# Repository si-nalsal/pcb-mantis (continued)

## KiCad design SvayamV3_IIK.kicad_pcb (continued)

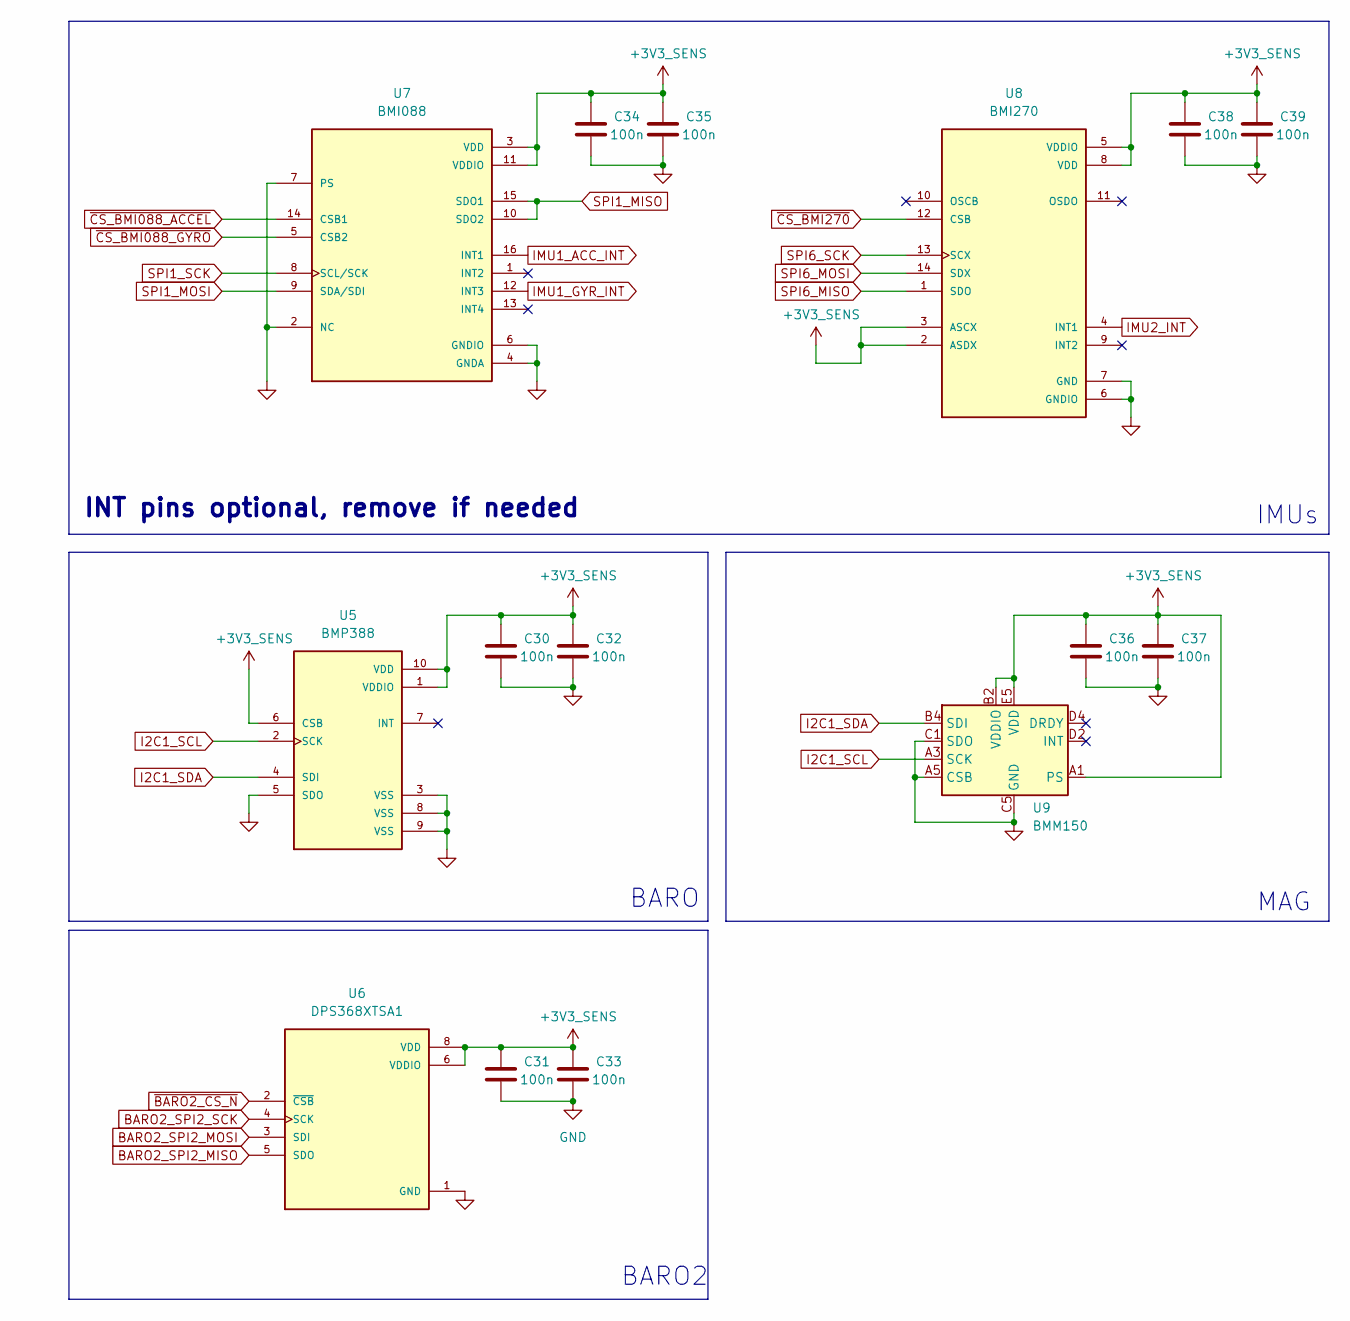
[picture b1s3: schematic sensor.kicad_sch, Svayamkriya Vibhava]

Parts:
C30, C31, C32, C33, C34, C35, C36, C37, C38, C39: 100n; C_0402_1005Metric; MPN CL05B104KB54PNC; LCSC C307331
U5: BMP388; XDCR_BMP388; PARTREV 1.1; LCSC C779278
U6: DPS368XTSA1; XDCR_DPS310XTSA1; MPN DPS368XTSA1; LCSC C3232508
U7: BMI088; PQFN50P450X300X100-16N; MPN BMI088; LCSC C194919
U8: BMI270; XDCR_BMI270; MPN BMI270; LCSC C2836813
U9: BMM150; WLCSP-12_1.56x1.56mm_P0.4mm; MPN BMM150; LCSC C171681

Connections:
+3V3_SENS: C30.1, C31.1, C32.1, C33.1, C34.1, C35.1, C36.1, C37.1, C38.1, C39.1, U5.1 (VDDIO), U5.6 (CSB), U5.10 (VDD), U6.6 (VDDIO), U6.8 (VDD), U7.3 (VDD), U7.11 (VDDIO), U8.2 (ASDX), U8.3 (ASCX), U8.5 (VDDIO), U8.8 (VDD), U9.A1 (PS), U9.B2 (VDDIO), U9.E5 (VDD); also elsewhere on the board
BARO2_SPI2_MISO: U6.5 (SDO); also elsewhere on the board
BARO2_SPI2_MOSI: U6.3 (SDI); also elsewhere on the board
BARO2_SPI2_SCK: U6.4 (SCK); also elsewhere on the board
GND: C30.2, C31.2, C32.2, C33.2, C34.2, C35.2, C36.2, C37.2, C38.2, C39.2, U5.3 (VSS), U5.5 (SDO), U5.8 (VSS), U5.9 (VSS), U6.1 (GND), U6.7 (GND), U7.2 (NC), U7.4 (GNDA), U7.6 (GNDIO), U7.7 (PS), U8.6 (GNDIO), U8.7 (GND), U9.A5 (CSB), U9.C1 (SDO), U9.C5 (GND), U9.E1 (GND), U9.E3 (GND); also elsewhere on the board
I2C1_SCL: U5.2 (SCK), U9.A3 (SCK); also elsewhere on the board
I2C1_SDA: U5.4 (SDI), U9.B4 (SDI); also elsewhere on the board
IMU1_ACC_INT: U7.16 (INT1); also elsewhere on the board
IMU1_GYR_INT: U7.12 (INT3); also elsewhere on the board
IMU2_INT: U8.4 (INT1); also elsewhere on the board
SPI1_MISO: U7.10 (SDO2), U7.15 (SDO1); also elsewhere on the board
SPI1_MOSI: U7.9 (SDA/SDI); also elsewhere on the board
SPI1_SCK: U7.8 (SCL/SCK); also elsewhere on the board
SPI6_MISO: U8.1 (SDO); also elsewhere on the board
SPI6_MOSI: U8.14 (SDX); also elsewhere on the board
SPI6_SCK: U8.13 (SCX); also elsewhere on the board
~BARO2_CS_N: U6.2 (~CSB); also elsewhere on the board
~CS_BMI088_ACCEL: U7.14 (CSB1); also elsewhere on the board
~CS_BMI088_GYRO: U7.5 (CSB2); also elsewhere on the board
~CS_BMI270: U8.12 (CSB); also elsewhere on the board

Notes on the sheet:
MAG
BARO2
IMUs
BARO
INT pins optional, remove if needed

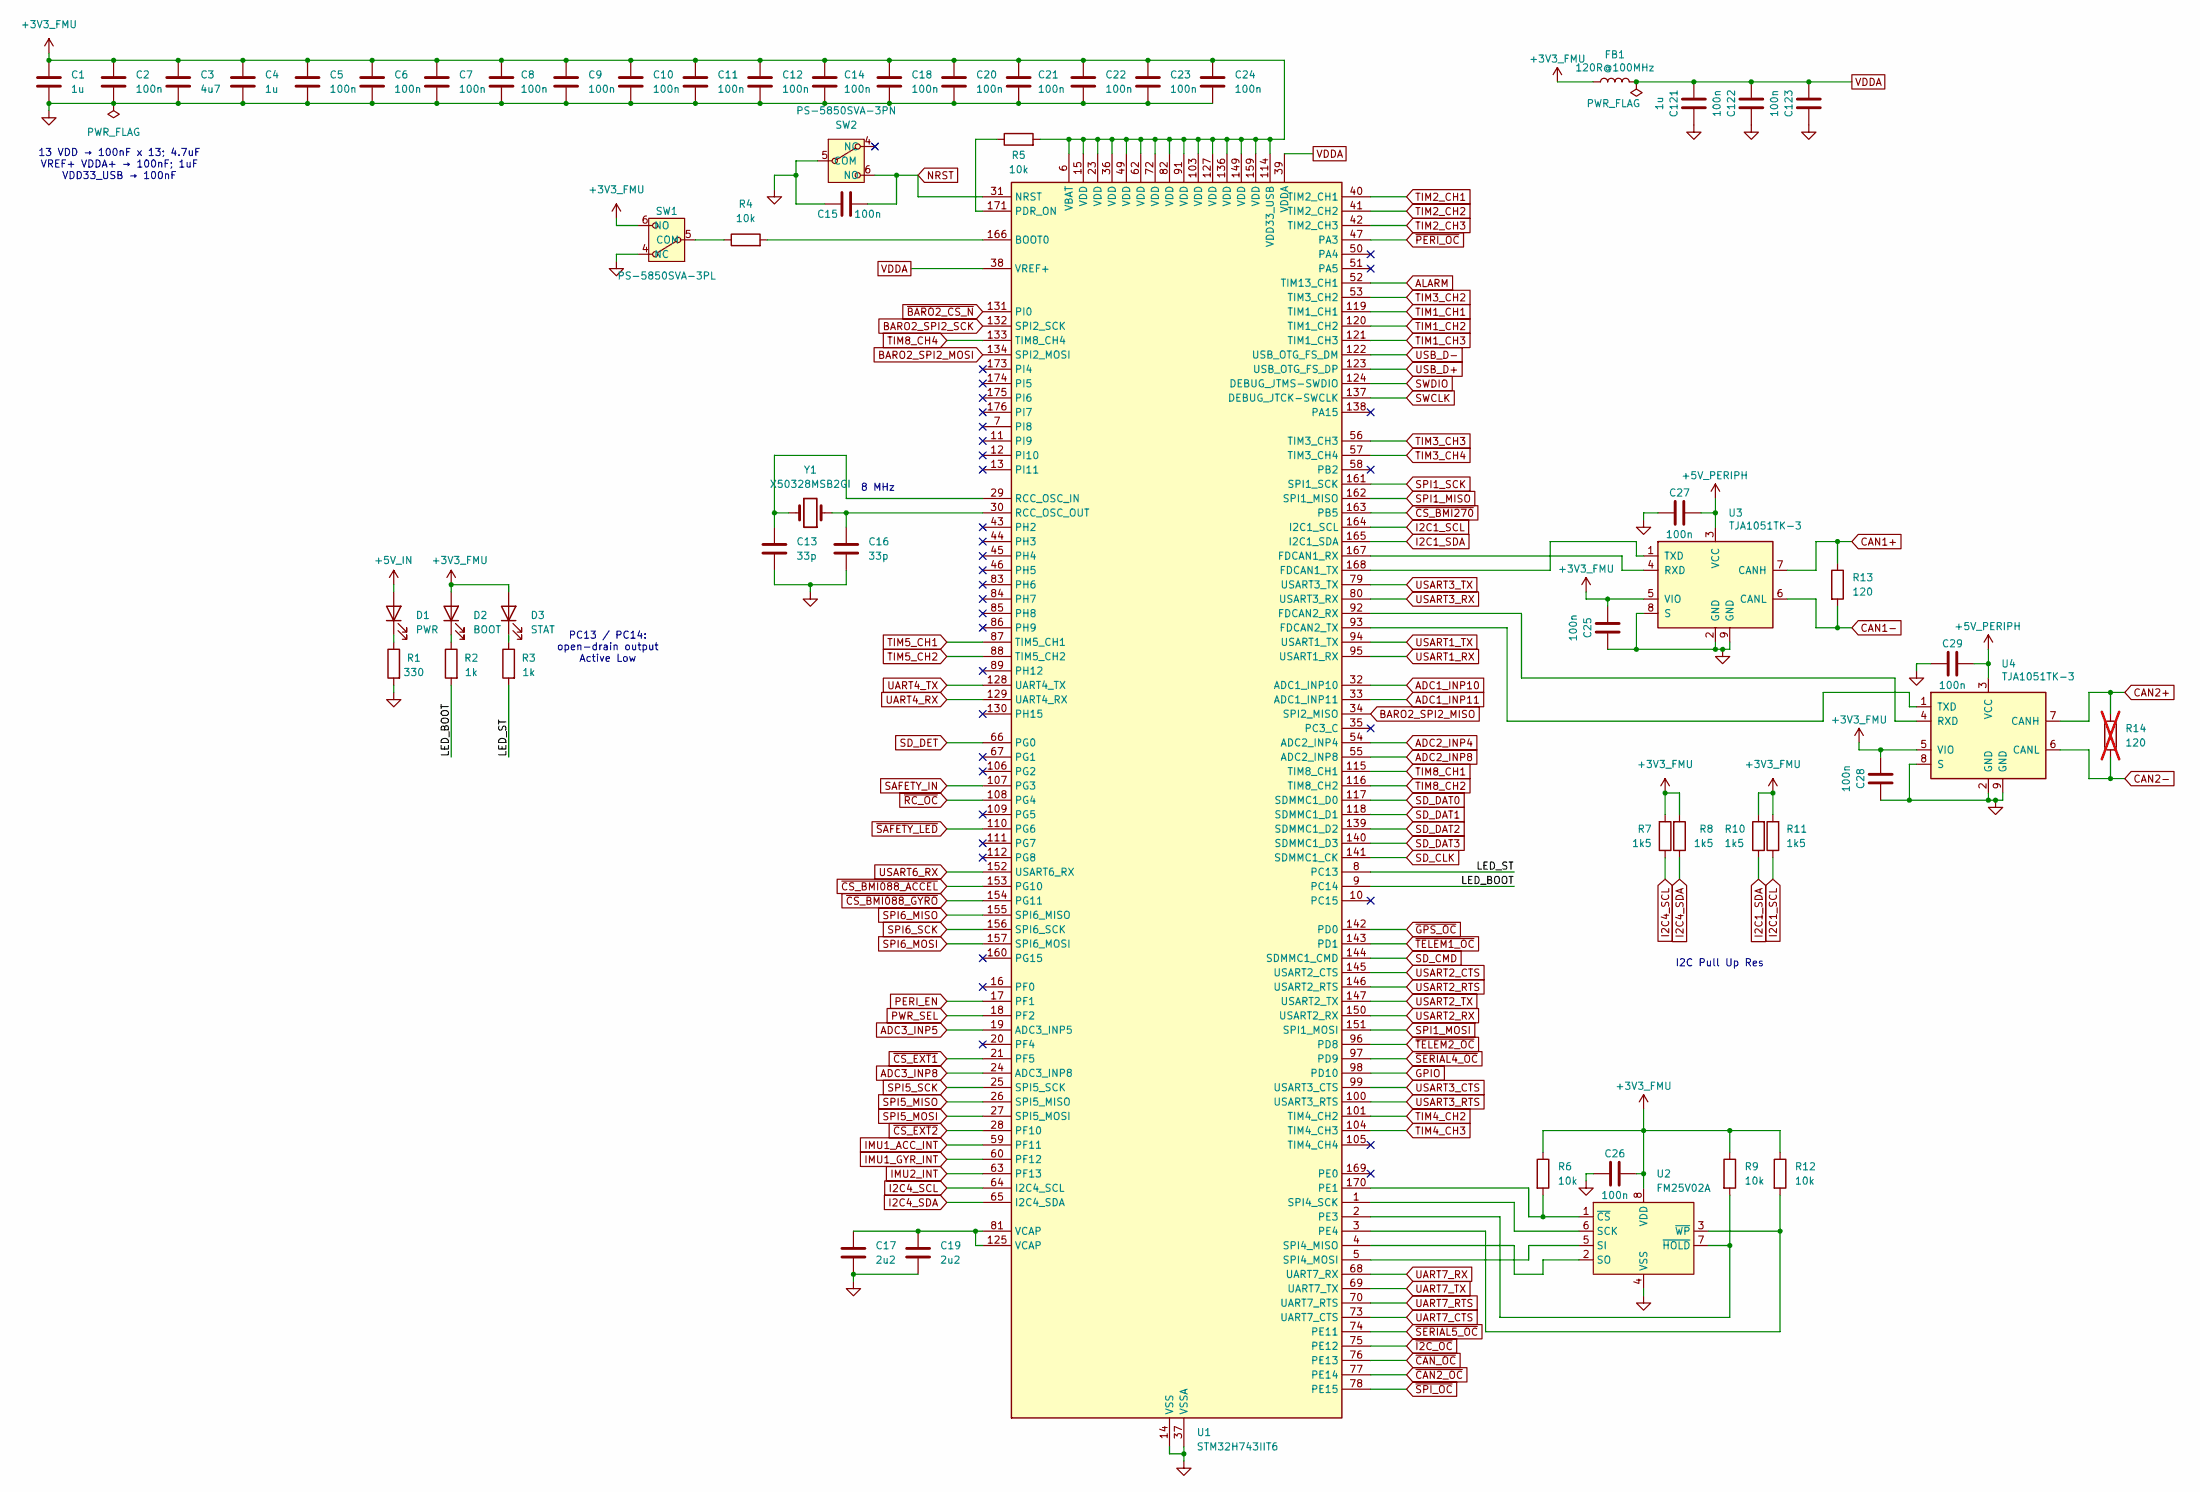
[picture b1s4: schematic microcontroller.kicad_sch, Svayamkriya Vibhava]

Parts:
C1, C4, C121: 1u; C_0603_1608Metric; MPN CL10A105KB8NNNC; LCSC C15849
C2, C5, C6, C7, C8, C9, C10, C11, C12, C14, C15, C18, C20, C21, C22, C23, C24, C25, C26, C27, C28, C29, C122, C123: 100n; C_0402_1005Metric; MPN CL05B104KB54PNC; LCSC C307331
C3: 4u7; C_0603_1608Metric; MPN CL10A475KO8NNNC; LCSC C19666
C13, C16: 33p; C_0402_1005Metric; MPN 0402CG330J500NT; LCSC C1562
C17, C19: 2u2; C_0603_1608Metric; MPN CL10A225KO8NNNC; LCSC C23630
D1: PWR; D_0603_1608Metric; MPN NCD0603R1; LCSC C84263
D2: BOOT; D_0603_1608Metric; MPN NCD0603R1; LCSC C84263
D3: STAT; D_0603_1608Metric; MPN NCD0603R1; LCSC C84263
FB1: 120R@100MHz; L_0402_1005Metric; MPN BLM15PD121SN1D; LCSC C76891
R1: 330; R_0402_1005Metric; MPN 0402WGF3300TCE; LCSC C25104
R2, R3: 1k; R_0402_1005Metric; MPN 0402WGF1001TCE; LCSC C11702
R4, R5, R6, R9, R12: 10k; R_0402_1005Metric; MPN 0402WGF1002TCE; LCSC C25744
R7, R8, R10, R11: 1k5; R_0402_1005Metric; MPN 0402WGF1501TCE; LCSC C25867
R13: 120; R_0402_1005Metric; MPN 0402WGF1200TCE; LCSC C25079
R14: 120; R_0402_1005Metric; MPN 0402WGF1200TCE; LCSC C25079; not fitted
SW1: PS-5850SVA-3PL; SW-SMD_G-SWITCH_PS-5850SVX-3PL; MPN PS-5850SVA-3PL; LCSC C5155594
SW2: PS-5850SVA-3PN; SW-SMD_G-SWITCH_PS-5850SVX-3PL; MPN PS-5850SVA-3PN; LCSC C5155595
U1: STM32H743IIT6; LQFP-176_24x24mm_P0.5mm; MPN STM32H743IIT6; LCSC C89597
U2: FM25V02A; SOIC-8_3.9x4.9mm_P1.27mm; MPN FM25V02A-GTR; LCSC C66029
U3, U4: TJA1051TK-3; DFN-8-1EP_3x3mm_P0.65mm_EP1.55x2.4mm; MPN TJA1051TK/3,118; LCSC C124020
Y1: X50328MSB2GI; Crystal_SMD_5032-2Pin_5.0x3.2mm; MPN X50328MSB2GI; LCSC C115962

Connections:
+3V3_FMU: C1.1, C2.1, C3.1, C4.1, C5.1, C6.1, C7.1, C8.1, C9.1, C10.1, C11.1, C12.1, C14.1, C18.1, C20.1, C21.1, C22.1, C23.1, C24.1, C25.1, C26.2, C28.1, D2.2 (A), D3.2 (A), FB1.1, R5.2, R6.1, R7.2, R8.2, R9.1, R10.2, R11.2, R12.1, SW1.6 (NO), U1.6 (VBAT), U1.15 (VDD), U1.23 (VDD), U1.36 (VDD), U1.49 (VDD), U1.62 (VDD), U1.72 (VDD), U1.82 (VDD), U1.91 (VDD), U1.103 (VDD), U1.114 (VDD33_USB), U1.127 (VDD), U1.136 (VDD), U1.149 (VDD), U1.159 (VDD), U1.172 (VDD), U2.8 (VDD), U3.5 (VIO), U4.5 (VIO); also elsewhere on the board
+5V_IN: D1.2 (A); also elsewhere on the board
+5V_PERIPH: C27.2, C29.2, U3.3 (VCC), U4.3 (VCC); also elsewhere on the board
/Microcontroller/LED_BOOT: R2.2, U1.9 (PC14)
/Microcontroller/LED_ST: R3.2, U1.8 (PC13)
ADC1_INP10: U1.32 (ADC1_INP10); also elsewhere on the board
ADC1_INP11: U1.33 (ADC1_INP11); also elsewhere on the board
ADC2_INP4: U1.54 (ADC2_INP4); also elsewhere on the board
ADC2_INP8: U1.55 (ADC2_INP8); also elsewhere on the board
ADC3_INP5: U1.19 (ADC3_INP5); also elsewhere on the board
ADC3_INP8: U1.24 (ADC3_INP8); also elsewhere on the board
ALARM: U1.52 (TIM13_CH1); also elsewhere on the board
BARO2_SPI2_MISO: U1.34 (SPI2_MISO); also elsewhere on the board
BARO2_SPI2_MOSI: U1.134 (SPI2_MOSI); also elsewhere on the board
BARO2_SPI2_SCK: U1.132 (SPI2_SCK); also elsewhere on the board
CAN1+: R13.1, U3.7 (CANH); also elsewhere on the board
CAN1-: R13.2, U3.6 (CANL); also elsewhere on the board
CAN2+: R14.1, U4.7 (CANH); also elsewhere on the board
CAN2-: R14.2, U4.6 (CANL); also elsewhere on the board
GND: C1.2, C2.2, C3.2, C4.2, C5.2, C6.2, C7.2, C8.2, C9.2, C10.2, C11.2, C12.2, C13.2, C14.2, C15.1, C16.2, C17.2, C18.2, C19.2, C20.2, C21.2, C22.2, C23.2, C24.2, C25.2, C26.1, C27.1, C28.2, C29.1, C121.2, C122.2, C123.2, R1.2, SW1.4 (NC), SW2.5 (COM), U1.14 (VSS), U1.22 (VSS), U1.37 (VSSA), U1.48 (VSS), U1.61 (VSS), U1.71 (VSS), U1.90 (VSS), U1.102 (VSS), U1.113 (VSS), U1.126 (VSS), U1.135 (VSS), U1.148 (VSS), U1.158 (VSS), U2.4 (VSS), U3.2 (GND), U3.8 (S), U3.9 (GND), U4.2 (GND), U4.8 (S), U4.9 (GND); also elsewhere on the board
GPIO: U1.98 (PD10); also elsewhere on the board
I2C1_SCL: R11.1, U1.164 (I2C1_SCL); also elsewhere on the board
I2C1_SDA: R10.1, U1.165 (I2C1_SDA); also elsewhere on the board
I2C4_SCL: R7.1, U1.64 (I2C4_SCL); also elsewhere on the board
I2C4_SDA: R8.1, U1.65 (I2C4_SDA); also elsewhere on the board
IMU1_ACC_INT: U1.59 (PF11); also elsewhere on the board
IMU1_GYR_INT: U1.60 (PF12); also elsewhere on the board
IMU2_INT: U1.63 (PF13); also elsewhere on the board
NRST: C15.2, SW2.6 (NO), U1.31 (NRST); also elsewhere on the board
unnamed: C17.1, C19.1, U1.81 (VCAP), U1.125 (VCAP)
unnamed: D1.1 (K), R1.1
unnamed: D2.1 (K), R2.1
unnamed: D3.1 (K), R3.1
unnamed: R4.1, SW1.5 (COM)
unnamed: R4.2, U1.166 (BOOT0)
unnamed: U1.167 (FDCAN1_RX), U3.4 (RXD)
unnamed: U1.168 (FDCAN1_TX), U3.1 (TXD)
unnamed: U1.92 (FDCAN2_RX), U4.4 (RXD)
unnamed: U1.93 (FDCAN2_TX), U4.1 (TXD)
unnamed: R5.1, U1.171 (PDR_ON)
unnamed: R6.2, U1.170 (PE1), U2.1 (~CS)
unnamed: U1.1 (SPI4_SCK), U2.6 (SCK)
unnamed: R9.2, U1.2 (PE3), U2.7 (~HOLD)
unnamed: R12.2, U1.3 (PE4), U2.3 (~WP)
unnamed: U1.4 (SPI4_MISO), U2.2 (SO)
unnamed: U1.5 (SPI4_MOSI), U2.5 (SI)
unnamed: C13.1, U1.29 (RCC_OSC_IN), Y1.2
unnamed: C16.1, U1.30 (RCC_OSC_OUT), Y1.1
PERI_EN: U1.17 (PF1); also elsewhere on the board
PWR_SEL: U1.18 (PF2); also elsewhere on the board
SAFETY_IN: U1.107 (PG3); also elsewhere on the board
SD_CLK: U1.141 (SDMMC1_CK); also elsewhere on the board
SD_CMD: U1.144 (SDMMC1_CMD); also elsewhere on the board
SD_DAT0: U1.117 (SDMMC1_D0); also elsewhere on the board
SD_DAT1: U1.118 (SDMMC1_D1); also elsewhere on the board
SD_DAT2: U1.139 (SDMMC1_D2); also elsewhere on the board
SD_DAT3: U1.140 (SDMMC1_D3); also elsewhere on the board
SD_DET: U1.66 (PG0); also elsewhere on the board
SPI1_MISO: U1.162 (SPI1_MISO); also elsewhere on the board
SPI1_MOSI: U1.151 (SPI1_MOSI); also elsewhere on the board
SPI1_SCK: U1.161 (SPI1_SCK); also elsewhere on the board
SPI5_MISO: U1.26 (SPI5_MISO); also elsewhere on the board
SPI5_MOSI: U1.27 (SPI5_MOSI); also elsewhere on the board
SPI5_SCK: U1.25 (SPI5_SCK); also elsewhere on the board
SPI6_MISO: U1.155 (SPI6_MISO); also elsewhere on the board
SPI6_MOSI: U1.157 (SPI6_MOSI); also elsewhere on the board
SPI6_SCK: U1.156 (SPI6_SCK); also elsewhere on the board
SWCLK: U1.137 (DEBUG_JTCK-SWCLK); also elsewhere on the board
SWDIO: U1.124 (DEBUG_JTMS-SWDIO); also elsewhere on the board
TIM1_CH1: U1.119 (TIM1_CH1); also elsewhere on the board
TIM1_CH2: U1.120 (TIM1_CH2); also elsewhere on the board
TIM1_CH3: U1.121 (TIM1_CH3); also elsewhere on the board
TIM2_CH1: U1.40 (TIM2_CH1); also elsewhere on the board
TIM2_CH2: U1.41 (TIM2_CH2); also elsewhere on the board
TIM2_CH3: U1.42 (TIM2_CH3); also elsewhere on the board
TIM3_CH2: U1.53 (TIM3_CH2); also elsewhere on the board
TIM3_CH3: U1.56 (TIM3_CH3); also elsewhere on the board
TIM3_CH4: U1.57 (TIM3_CH4); also elsewhere on the board
TIM4_CH2: U1.101 (TIM4_CH2); also elsewhere on the board
TIM4_CH3: U1.104 (TIM4_CH3); also elsewhere on the board
TIM5_CH1: U1.87 (TIM5_CH1); also elsewhere on the board
TIM5_CH2: U1.88 (TIM5_CH2); also elsewhere on the board
TIM8_CH1: U1.115 (TIM8_CH1); also elsewhere on the board
TIM8_CH2: U1.116 (TIM8_CH2); also elsewhere on the board
TIM8_CH4: U1.133 (TIM8_CH4); also elsewhere on the board
UART4_RX: U1.129 (UART4_RX); also elsewhere on the board
UART4_TX: U1.128 (UART4_TX); also elsewhere on the board
UART7_CTS: U1.73 (UART7_CTS); also elsewhere on the board
UART7_RTS: U1.70 (UART7_RTS); also elsewhere on the board
UART7_RX: U1.68 (UART7_RX); also elsewhere on the board
UART7_TX: U1.69 (UART7_TX); also elsewhere on the board
USART1_RX: U1.95 (USART1_RX); also elsewhere on the board
USART1_TX: U1.94 (USART1_TX); also elsewhere on the board
USART2_CTS: U1.145 (USART2_CTS); also elsewhere on the board
USART2_RTS: U1.146 (USART2_RTS); also elsewhere on the board
USART2_RX: U1.150 (USART2_RX); also elsewhere on the board
USART2_TX: U1.147 (USART2_TX); also elsewhere on the board
USART3_CTS: U1.99 (USART3_CTS); also elsewhere on the board
USART3_RTS: U1.100 (USART3_RTS); also elsewhere on the board
USART3_RX: U1.80 (USART3_RX); also elsewhere on the board
USART3_TX: U1.79 (USART3_TX); also elsewhere on the board
USART6_RX: U1.152 (USART6_RX); also elsewhere on the board
USB_D+: U1.123 (USB_OTG_FS_DP); also elsewhere on the board
USB_D-: U1.122 (USB_OTG_FS_DM); also elsewhere on the board
VDDA: C121.1, C122.1, C123.1, FB1.2, U1.38 (VREF+), U1.39 (VDDA)
~BARO2_CS_N: U1.131 (PI0); also elsewhere on the board
~CAN2_OC: U1.77 (PE14); also elsewhere on the board
~CAN_OC: U1.76 (PE13); also elsewhere on the board
~CS_BMI088_ACCEL: U1.153 (PG10); also elsewhere on the board
~CS_BMI088_GYRO: U1.154 (PG11); also elsewhere on the board
~CS_BMI270: U1.163 (PB5); also elsewhere on the board
~CS_EXT1: U1.21 (PF5); also elsewhere on the board
~CS_EXT2: U1.28 (PF10); also elsewhere on the board
~GPS_OC: U1.142 (PD0); also elsewhere on the board
~I2C_OC: U1.75 (PE12); also elsewhere on the board
~PERI_OC: U1.47 (PA3); also elsewhere on the board
~RC_OC: U1.108 (PG4); also elsewhere on the board
~SAFETY_LED: U1.110 (PG6); also elsewhere on the board
~SERIAL4_OC: U1.97 (PD9); also elsewhere on the board
~SERIAL5_OC: U1.74 (PE11); also elsewhere on the board
~SPI_OC: U1.78 (PE15); also elsewhere on the board
~TELEM1_OC: U1.143 (PD1); also elsewhere on the board
~TELEM2_OC: U1.96 (PD8); also elsewhere on the board

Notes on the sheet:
8 MHz
I2C Pull Up Res
13 VDD → 100nF x 13; 4.7uF VREF+ VDDA+ → 100nF; 1uF VDD33_USB → 100nF
PC13 / PC14: open-drain output Active Low

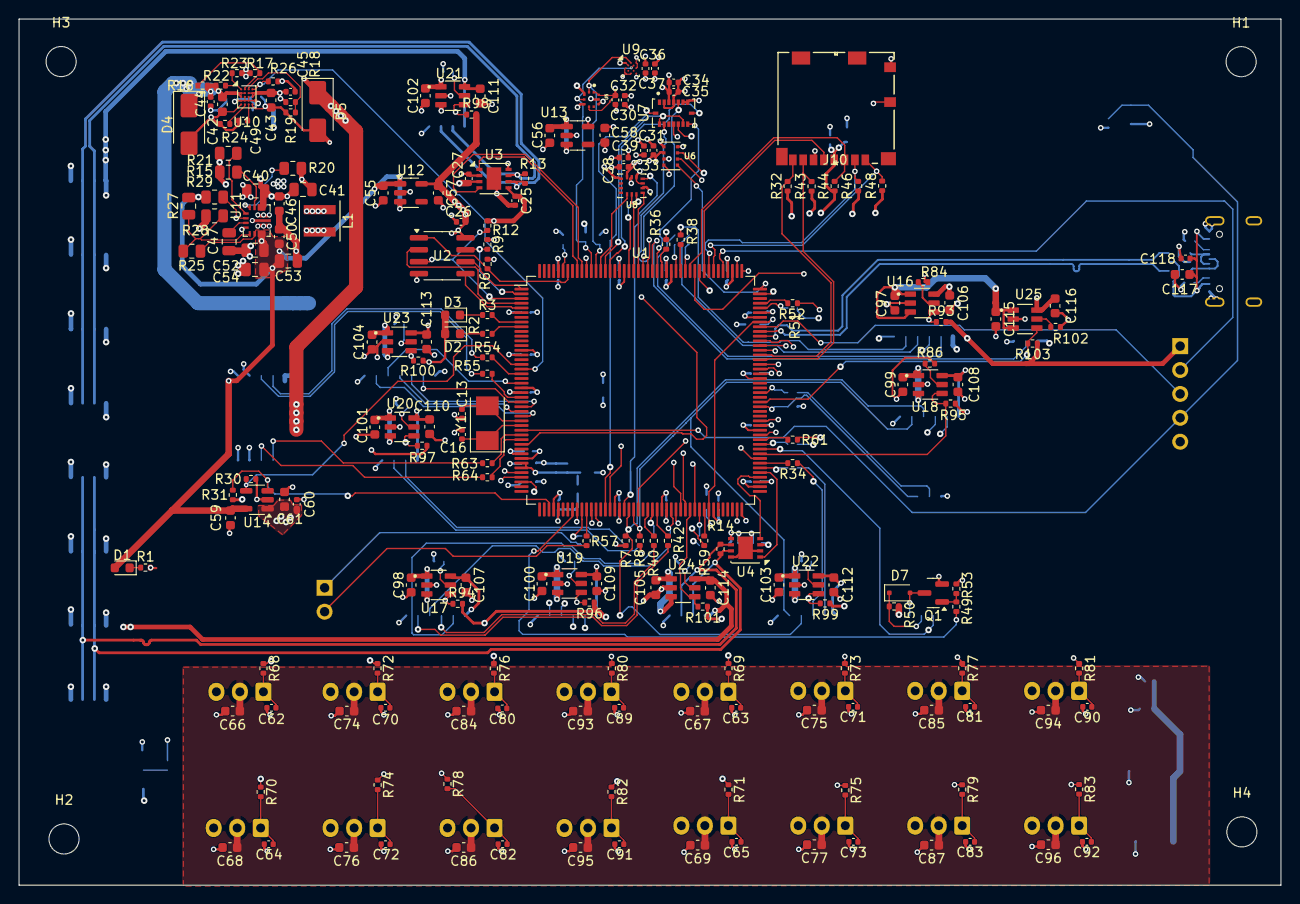
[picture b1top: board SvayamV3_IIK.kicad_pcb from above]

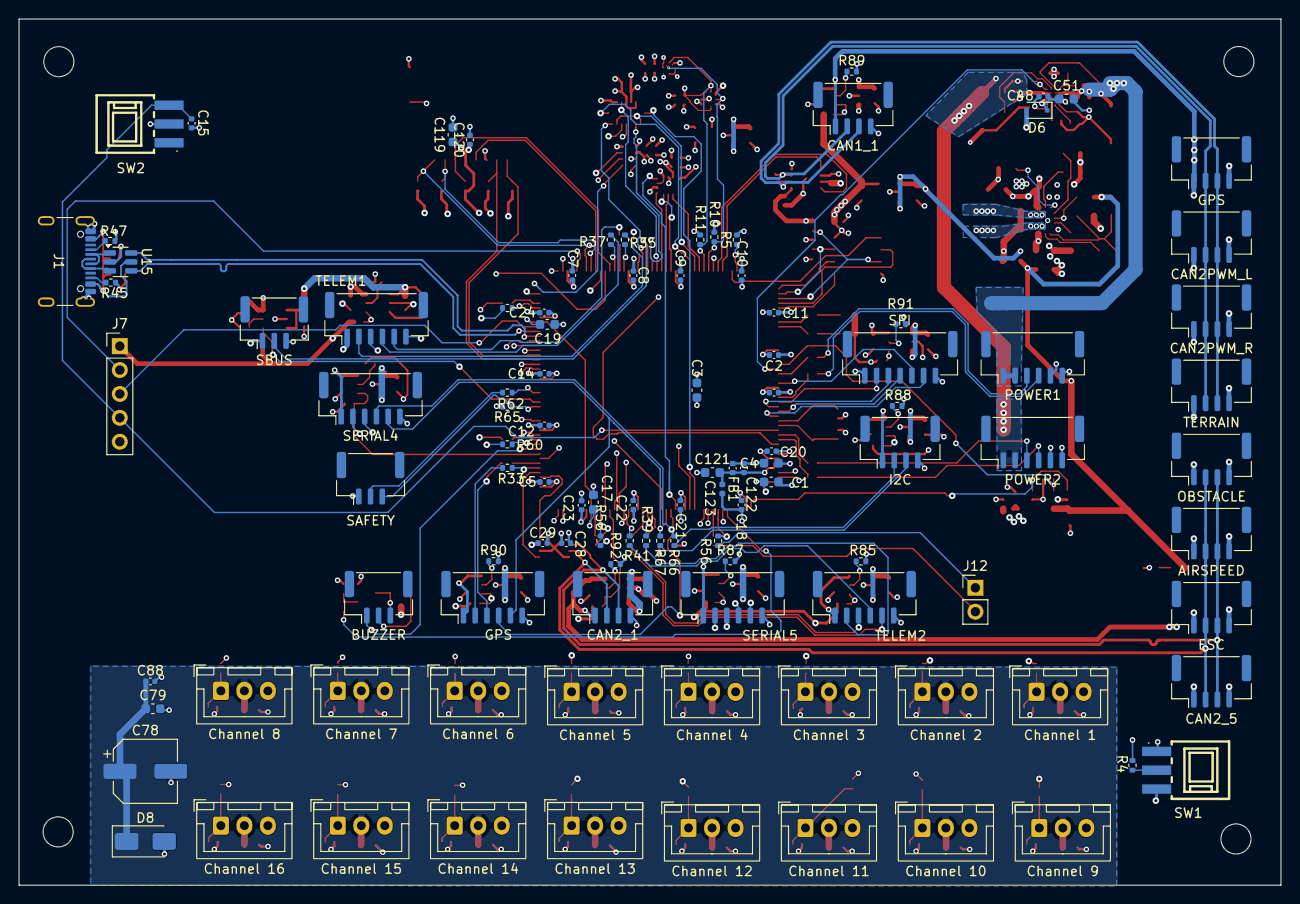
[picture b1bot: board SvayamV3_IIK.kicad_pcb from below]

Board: 6 copper layers, 134.1 x 92.1 mm, 311 parts (107 on the bottom side), 211 nets.

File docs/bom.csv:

"Refs","Value","Footprint","MPN","LCSC"
"C1,C4,C59,C66-C69,C74-C77,C79,C84-C87,C93-C114","1u","Capacitor_SMD:C_0603_1608Metric","CL10A105KB8NNNC",""
"C2,C5-C12,C14,C15,C18,C20-C39,C44,C45,C48,C49,C60,C62-C65,C70-C73,C80-C83,C88-C92","100n","Capacitor_SMD:C_0402_1005Metric","CL05B104KB54PNC",""
"C3,C42,C43,C55-C58","4u7","Capacitor_SMD:C_0603_1608Metric","CL10A475KO8NNNC",""
"C13,C16","33p","Capacitor_SMD:C_0402_1005Metric","0402CG330J500NT",""
"C17,C19","2u2","Capacitor_SMD:C_0603_1608Metric","CL10A225KO8NNNC",""
"C40,C41","10u","Capacitor_SMD:C_0805_2012Metric","",""
"C46,C50,C51,C61","10u","Capacitor_SMD:C_0603_1608Metric","CL10A106MA8NRNC",""
"C47","100n","Capacitor_SMD:C_0805_2012Metric","",""
"C52-C54","22u","Capacitor_SMD:C_0805_2012Metric","",""
"C78","220u","Capacitor_SMD:CP_Elec_6.3x7.7","",""
"D1","PWR","Diode_SMD:D_0603_1608Metric","NCD0603R1",""
"D2","BOOT","Diode_SMD:D_0603_1608Metric","NCD0603R1",""
"D3","STAT","Diode_SMD:D_0603_1608Metric","NCD0603R1",""
"D4,D5,D8","SMAJ6.0A","Diode_SMD:D_SMA","",""
"D6,D7","PMEG1030EJ,115","Diode_SMD:D_SOD-323F","PMEG1030EJ,115",""
"J1","USB_C_Receptacle_USB2.0_16P","easyeda2kicad:USB-C-SMD_TYPE-C16PIN","TYPE-C16PIN",""
"J2","GPS","Connector_JST:JST_GH_BM06B-GHS-TBT_1x06-1MP_P1.25mm_Vertical","",""
"J3","SPI","Connector_JST:JST_GH_BM07B-GHS-TBT_1x07-1MP_P1.25mm_Vertical","",""
"J4","TELEM1","Connector_JST:JST_GH_BM06B-GHS-TBT_1x06-1MP_P1.25mm_Vertical","",""
"J5","TELEM2","Connector_JST:JST_GH_BM06B-GHS-TBT_1x06-1MP_P1.25mm_Vertical","",""
"J6","SBUS","Connector_JST:JST_GH_BM03B-GHS-TBT_1x03-1MP_P1.25mm_Vertical","",""
"J7","Conn_01x05_Pin","Connector_PinHeader_2.54mm:PinHeader_1x05_P2.54mm_Vertical","",""
"J8","SERIAL4","Connector_JST:JST_GH_BM06B-GHS-TBT_1x06-1MP_P1.25mm_Vertical","",""
"J9","POWER1","Connector_JST:JST_GH_BM06B-GHS-TBT_1x06-1MP_P1.25mm_Vertical","",""
"J10","Micro_SD_Card_Det1","Svayam:104031-0811_MOL","1040310811",""
"J11","BUZZER","Connector_JST:JST_GH_BM03B-GHS-TBT_1x03-1MP_P1.25mm_Vertical","",""
"J12","ADC","Connector_PinHeader_2.54mm:PinHeader_1x02_P2.54mm_Vertical","",""
"J13","CAN","Connector_JST:JST_GH_BM04B-GHS-TBT_1x04-1MP_P1.25mm_Vertical","",""
"J14","SERIAL5","Connector_JST:JST_GH_BM06B-GHS-TBT_1x06-1MP_P1.25mm_Vertical","",""
"J15","SAFETY","Connector_JST:JST_GH_BM03B-GHS-TBT_1x03-1MP_P1.25mm_Vertical","",""
"J16","POWER2","Connector_JST:JST_GH_BM06B-GHS-TBT_1x06-1MP_P1.25mm_Vertical","",""
"J17","I2C","Connector_JST:JST_GH_BM04B-GHS-TBT_1x04-1MP_P1.25mm_Vertical","",""
"J18","CAN2","Connector_JST:JST_GH_BM04B-GHS-TBT_1x04-1MP_P1.25mm_Vertical","",""
"J19","Channel 1","Connector_JST:JST_XH_B3B-XH-A_1x03_P2.50mm_Vertical","",""
"J20","Channel 5","Connector_JST:JST_XH_B3B-XH-A_1x03_P2.50mm_Vertical","",""
"J21","Channel 9","Connector_JST:JST_XH_B3B-XH-A_1x03_P2.50mm_Vertical","",""
"J22","Channel 13","Connector_JST:JST_XH_B3B-XH-A_1x03_P2.50mm_Vertical","",""
"J23","Channel 2","Connector_JST:JST_XH_B3B-XH-A_1x03_P2.50mm_Vertical","",""
"J24","Channel 6","Connector_JST:JST_XH_B3B-XH-A_1x03_P2.50mm_Vertical","",""
"J25","Channel 10","Connector_JST:JST_XH_B3B-XH-A_1x03_P2.50mm_Vertical","",""
"J26","Channel 14","Connector_JST:JST_XH_B3B-XH-A_1x03_P2.50mm_Vertical","",""
"J27","Channel 3","Connector_JST:JST_XH_B3B-XH-A_1x03_P2.50mm_Vertical","",""
"J28","Channel 7","Connector_JST:JST_XH_B3B-XH-A_1x03_P2.50mm_Vertical","",""
"J29","Channel 11","Connector_JST:JST_XH_B3B-XH-A_1x03_P2.50mm_Vertical","",""
"J30","Channel 15","Connector_JST:JST_XH_B3B-XH-A_1x03_P2.50mm_Vertical","",""
"J31","Channel 4","Connector_JST:JST_XH_B3B-XH-A_1x03_P2.50mm_Vertical","",""
"J32","Channel 8","Connector_JST:JST_XH_B3B-XH-A_1x03_P2.50mm_Vertical","",""
"J33","Channel 12","Connector_JST:JST_XH_B3B-XH-A_1x03_P2.50mm_Vertical","",""
"J34","Channel 16","Connector_JST:JST_XH_B3B-XH-A_1x03_P2.50mm_Vertical","",""
"L1","1.5u","Svayam:L_Coilcraft_XxL4020","",""
"Q1","AO3400A","Package_TO_SOT_SMD:SOT-23","AO3400A",""
"R1","330","Resistor_SMD:R_0402_1005Metric","0402WGF3300TCE",""
"R2,R3,R7,R8,R10,R11,R65","1k5","Resistor_SMD:R_0402_1005Metric","0402WGF1501TCE",""
"R4-R6,R9,R12,R31,R53-R57,R63,R64","10k","Resistor_SMD:R_0402_1005Metric","0402WGF1002TCE",""
"R13,R14,R33-R42,R51,R52,R58-R61,R66-R83","120","Resistor_SMD:R_0402_1005Metric","0402WGF1200TCE",""
"R15,R21","10k","Resistor_SMD:R_0805_2012Metric","",""
"R16,R18","22k","Resistor_SMD:R_0402_1005Metric","0402WGF2202TCE",""
"R17,R19,R23,R45,R47,R49","5k1","Resistor_SMD:R_0402_1005Metric","0402WGF5101TCE",""
"R20,R25,R29","100k","Resistor_SMD:R_0805_2012Metric","",""
"R22","15k","Resistor_SMD:R_0402_1005Metric","0402WGF1502TCE",""
"R24,R84,R85","33k","Resistor_SMD:R_0402_1005Metric","0402WGF3302TCE",""
"R26,R30","100k","Resistor_SMD:R_0402_1005Metric","0402WGF1003TCE",""
"R27","68k","Resistor_SMD:R_0805_2012Metric","",""
"R28","13k","Resistor_SMD:R_0805_2012Metric","",""
"R32,R43,R44,R46,R48","51k","Resistor_SMD:R_0402_1005Metric","0402WGF5102TCE",""
"R50","10","Resistor_SMD:R_0402_1005Metric","0402WGF100JTCE",""
"R62","49.9","Resistor_SMD:R_0402_1005Metric","0402WGF499JTCE",""
"R86,R87","75k","Resistor_SMD:R_0402_1005Metric","",""
"R88,R91","110k","Resistor_SMD:R_0402_1005Metric","",""
"R89,R92","47k","Resistor_SMD:R_0402_1005Metric","",""
"R90","56k","Resistor_SMD:R_0402_1005Metric","",""
"SW1","SK-3296S-01-L3","easyeda2kicad:SW-SMD_SK-3296S-01-L3","SK-3296S-01-L3",""
"SW2","TS-1010A-B","easyeda2kicad:SW-SMD_TS-1010A-B","TS-1010A-B",""
"U1","STM32H743IIK6","Package_BGA:UFBGA-201_10x10mm_Layout15x15_P0.65mm","STM32H743IIK6",""
"U2","FM25CL64B","Package_SO:SOIC-8_3.9x4.9mm_P1.27mm","FM25CL64B-GTR",""
"U3,U4","TJA1051TK-3","Package_DFN_QFN:DFN-8-1EP_3x3mm_P0.65mm_EP1.55x2.4mm","TJA1051TK/3,118",""
"U5","BMP388","Svayam:XDCR_BMP388","BMP388",""
"U6","DPS310XTSA1","Svayam:XDCR_DPS310XTSA1","",""
"U7","BMI088","Svayam:PQFN50P450X300X100-16N","BMI088",""
"U8","BMI270","Svayam:XDCR_BMI270","BMI270",""
"U9","BMM150","Package_CSP:WLCSP-12_1.56x1.56mm_P0.4mm","BMM150",""
"U10","TPS2120YFPR","Package_BGA:Texas_YFP0020_DSBGA-20_1.588x1.988mm_Layout4x5_P0.4mm","TPS2120YFPR",""
"U11","TPS63070","Svayam:VQFN-HR-15","",""
"U12,U13","RT9080-33GJ5","Package_TO_SOT_SMD:TSOT-23-5","RT9080-33GJ5",""
"U14","AP22804AW5","Package_TO_SOT_SMD:SOT-23-5","AP22804AW5-7",""
"U15","USBLC6-2SC6","Package_TO_SOT_SMD:SOT-23-6","USBLC6-2SC6",""
"U16-U24","TPS2553DBVT","Svayam:SOT95P280X145-6N","",""
"Y1","X50328MSB2GI","Crystal:Crystal_SMD_5032-2Pin_5.0x3.2mm","X50328MSB2GI",""
